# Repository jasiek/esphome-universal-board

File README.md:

# [esphome.io](https://esphome.io)-compatible universal board

* Can control an air conditioning unit and read its remote to display current state of unit.
* Can drive multiple WS2812 LEDs to indicate something.
* Can drive a buzzer to indicate something.
* Notifications using the above can be acknowledged with a click of a button.
* Can read the state of a water meter which uses WMBUS using a CC1101 module.
* Can incorporate additional sensors via I2C.

## Parts

* ESP32 Module [ESP32-S3-WROOM-1](https://www.espressif.com/sites/default/files/documentation/esp32-s3-wroom-1_wroom-1u_datasheet_en.pdf)
* IR Receiver: [TSOP38438](https://www.vishay.com/docs/82491/tsop382.pdf)
* IR Transmitter 850nm @ 165mW: [LL-503SIRC2H-1BE](https://www.tme.eu/Document/bbc76b3f66c79fcebc4b2a3071fa53b8/LL-503SIRC2H-1BE.pdf)
* USB PD Controller: [CH224K](https://www.laskakit.cz/user/related_files/ch224ds1.pdf)
* CC1101 868MHz module: [Small](https://ae01.alicdn.com/kf/H425240e05325482f9e129bee543d8c9eR.jpg) or [Large](https://ae01.alicdn.com/kf/S28ad7d5c77624d52bd05b87e7f74fee7y.jpg)
* Level shifter: [74AHCT1G125](https://www.ti.com/lit/ds/symlink/sn74ahct1g125.pdf)
* Buzzer: [LPT1440S-HS-05](https://www.tme.eu/Document/ccb72bb5ba4b269fcfcf63562faa0900/LPT1440S-HS-05-4.0-12-R.pdf)
* Presence sensors
  * [HLK-LD2450](https://www.tinytronics.nl/product_files/006000_HLK-LD2450-Instruction-Manual.pdf)
  * [HLK-LD2402](https://drive.google.com/file/d/1SmigbSjFt1toA7W5wEuI2Qy-1CSR6PQn/view)
  * [HLK-LD2410](https://www.tinytronics.nl/product_files/006002_HLK-LD2410S_datasheet.pdf)

## Other

* [A Primer on USB Type-C® and USB Power Delivery Applications and Requirements](https://www.ti.com/lit/wp/slyy109b/slyy109b.pdf)

## TODO for rev 3

* Place everything on one side of the board!
* Use SMD electrolytic capacitors.
* Hook up the output of the WS2812 correctly.
* Holes in the board need to be slightly bigger.
* ~~22-33 ohm series resistors on the USB pins: USB-C <-> ESD <-> R <-> USB on ESP32.~~
* ~~Get rid of the 3A PSU circuit.~~
* ~~Replace LED transmitter with a 940nm part, for example TSAL6200 (narrow beam), OSI5LA56A1A, IR7393C (100mA), OSI5NE87B1A, IR323/H0-A, IR8294, OSI5LA7WA1B.~~
* ~~Add another footprint for WS2812B and WS2812S, so that either can be populated~~

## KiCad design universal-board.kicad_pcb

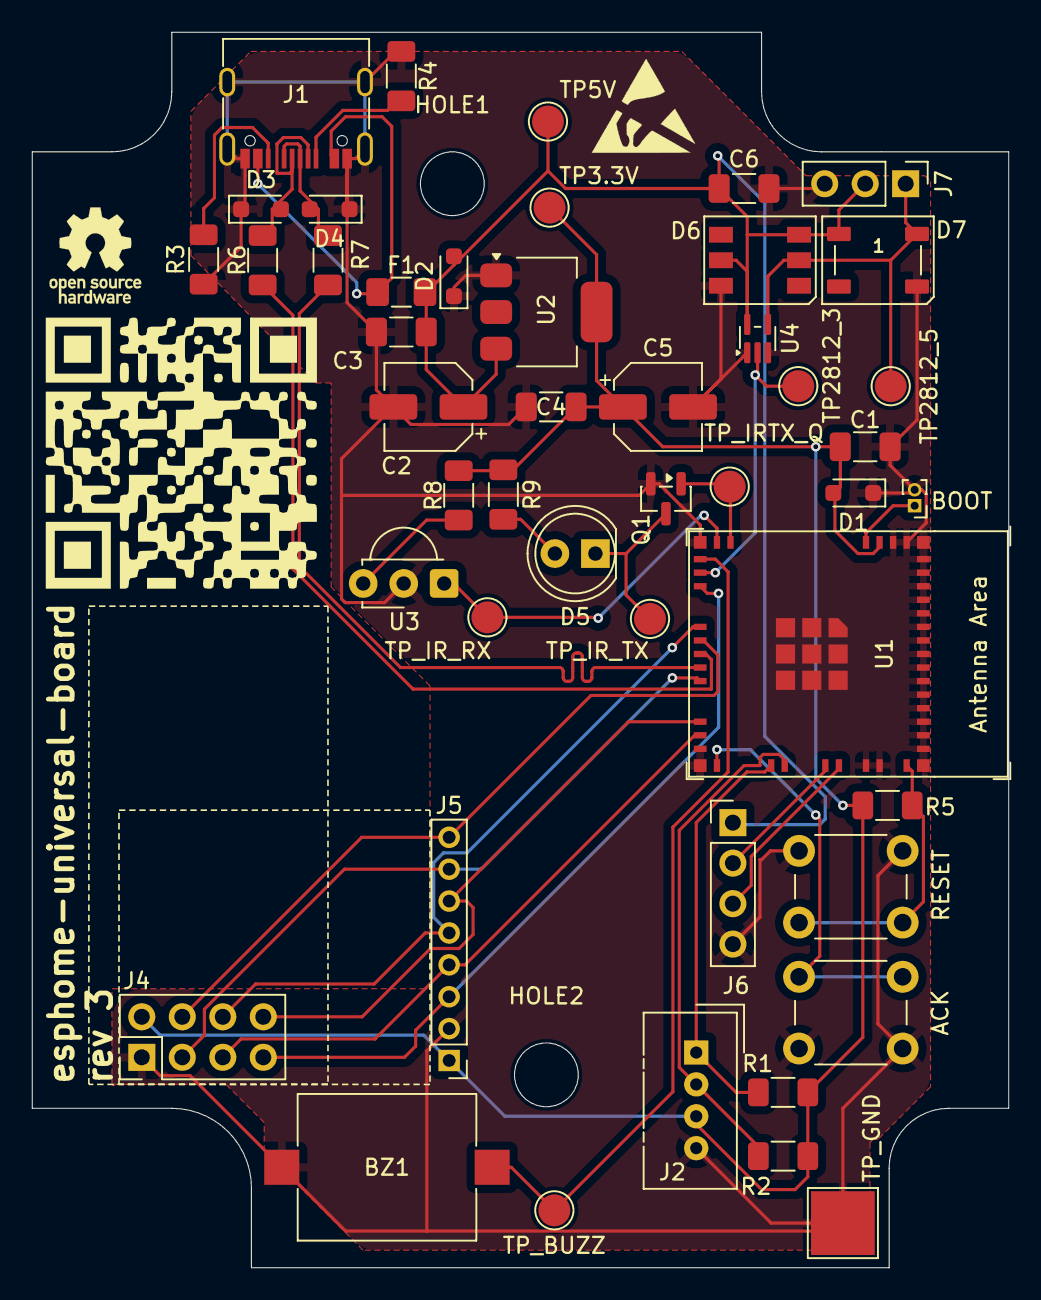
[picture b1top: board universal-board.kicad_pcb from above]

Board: 2 copper layers, 61.2 x 77.5 mm, 49 parts (0 on the bottom side), 31 nets.

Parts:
ACK: SW_ACK; SW_PUSH_6mm
BOOT: CONN_BOOT; PinHeader_1x02_P1.00mm_Vertical
BZ1: LPT1440S-HS-05; Buzzer_Mallory_AST1109MLTRQ
C1, C3, C4, C6: 100nF; C_1206_3216Metric_Pad1.33x1.80mm_HandSolder
C2: 10uF; CP_Elec_5x5.4
C5: 22uF; CP_Elec_5x5.4
D1, D2, D3, D4: PESD5V0L1BA,115-ES; D_SOD-323_HandSoldering
D5: IR7393C; LED_D5.0mm_Clear
D6: WS2812; LED_WS2812_PLCC6_5.0x5.0mm_P1.6mm
D7: WS2812B; LED_WS2812B_PLCC4_5.0x5.0mm_P3.2mm
F1: 0ZCJ0100FF2E (1A); Fuse_1206_3216Metric_Pad1.42x1.75mm_HandSolder
HOLE1, HOLE2: MountingHole_4mm
J1: USB_C_Receptacle; USB_C_Receptacle_G-Switch_GT-USB-7010ASV
J2: CONN_I2C_GROVE; NS-Tech_Grove_1x04_P2mm_Vertical
J4: CONN_CC1101_2; PinHeader_2x04_P2.54mm_Vertical
J5: CONN_CC1101_1; PinHeader_1x08_P2.00mm_Vertical
J6: CONN_UART; PinHeader_1x04_P2.54mm_Vertical
J7: CONN_WS2812; PinHeader_1x03_P2.54mm_Vertical
Q1: BSS138; SOT-23
R1, R2: 4.7k; R_1206_3216Metric_Pad1.30x1.75mm_HandSolder
R3, R4: 5.1k; R_1206_3216Metric_Pad1.30x1.75mm_HandSolder
R5: 10k; R_1206_3216Metric_Pad1.30x1.75mm_HandSolder
R6, R7, R9: 22; R_1206_3216Metric_Pad1.30x1.75mm_HandSolder
R8: 100; R_1206_3216Metric_Pad1.30x1.75mm_HandSolder
RESET: SW_RST; SW_PUSH_6mm
TP3.3V: TP_3.3V; TestPoint_Pad_D2.0mm
TP5V: TP_5V; TestPoint_Pad_D2.0mm
TP2812_3: TP_21812_3.3; TestPoint_Pad_D2.0mm
TP2812_5: TP_2812_5; TestPoint_Pad_D2.0mm
TP_BUZZ: TP_BUZZ; TestPoint_Pad_D2.0mm
TP_GND: TP_GND; TestPoint_Pad_4.0x4.0mm
TP_IRTX_Q: TP_IR_TX; TestPoint_Pad_D2.0mm
TP_IR_RX: TP_IR_RX; TestPoint_Pad_D2.0mm
TP_IR_TX: TP_IR_TX_OUT; TestPoint_Pad_D2.0mm
U1: ESP32-S2-MINI-2; ESP32-S2-MINI-1
U2: AMS1117-3.3; SOT-223-3_TabPin2
U3: TSOP384xx; Vishay_MINICAST-3Pin
U4: 74AHCT1G125; SOT-353_SC-70-5

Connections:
3.3V: C1.1, C4.1, C5.1, D1.2 (A2), J2.3, J4.2, J5.1, R1.2, R2.1, R5.2, R8.1, R9.1, TP3.3V.1, U1.3 (3V3), U2.2 (VO)
5V: C2.1, C3.1, C6.1, D2.2 (A2), D6.3 (VCC), D6.5 (VDD), D7.1 (VDD), F1.2, J6.1, J7.2, TP5V.1, U2.3 (VI), U4.5 (VCC)
BUZZ_OUT: BZ1.1 (+), TP_BUZZ.1, U1.16 (GPIO12/ADC2_CH1)
CSN: J4.4, J5.8, U1.22 (ADC2_CH7/DAC_2/GPIO18)
GDO0: J4.3, J5.7, U1.25 (GPIO21)
GDO2: J4.8, J5.6, U1.28 (GPIO33)
GND: ACK.2 (B), BOOT.2, BZ1.2 (-), C1.2, C2.2, C3.2, C4.2, C5.2, C6.2, D1.1 (A1), D2.1 (A1), D3.1 (A1), D4.1 (A1), D6.6 (VSS), D7.3 (VSS), J1.A1 (GND), J1.A12 (GND), J1.B1 (GND), J1.B12 (GND), J1.S1 (SHIELD), J2.4, J4.1, J5.2, J6.4, J7.3, Q1.2 (S), R3.1, R4.2, RESET.1 (A), TP_GND.1, U1.1 (GND), U1.2 (GND), U1.30 (GND), U1.42 (GND), U1.43 (GND), U1.46 (GND), U1.47 (GND), U1.48 (GND), U1.49 (GND), U1.50 (GND), U1.51 (GND), U1.52 (GND), U1.53 (GND), U1.54 (GND), U1.55 (GND), U1.56 (GND), U1.57 (GND), U1.58 (GND), U1.59 (GND), U1.60 (GND), U1.61 (GND), U1.62 (GND), U1.63 (GND), U1.64 (GND), U1.65 (GND), U2.1 (GND), U3.2 (GND), U4.1, U4.3 (GND)
IR_RX_OUT: TP_IR_RX.1, U1.15 (GPIO11/ADC2_CH0), U3.1 (OUT)
IR_TX_IN: Q1.1 (G), TP_IRTX_Q.1, U1.14 (GPIO10/ADC1_CH9)
MISO: J4.7, J5.3, U1.18 (GPIO14/ADC2_CH3)
MOSI: J4.6, J5.5, U1.21 (ADC2_CH6/DAC_1/GPIO17)
unnamed: D3.2 (A2), J1.A7 (D-), J1.B7 (D-), R6.1
unnamed: D4.2 (A2), J1.A6 (D+), J1.B6 (D+), R7.1
unnamed: D5.2 (A), R9.2
unnamed: D5.1 (K), Q1.3 (D), TP_IR_TX.1
unnamed: D6.2 (DIN), D7.4 (DIN), J7.1, TP2812_5.1, U4.4
unnamed: F1.1, J1.A4 (VBUS), J1.A9 (VBUS), J1.B4 (VBUS), J1.B9 (VBUS)
unnamed: J1.A5 (CC1), R4.1
unnamed: J1.B5 (CC2), R3.2
unnamed: J2.1, R1.1, U1.35 (MTCK/JTAG/GPIO39)
unnamed: J2.2, R2.2, U1.36 (MTDO/JTAG/GPIO40)
unnamed: BOOT.1, U1.4 (GPIO0/BOOT)
unnamed: R5.1, RESET.2 (B), U1.45 (CHIP/PU/RESET)
unnamed: R8.2, U3.3 (Vs)
SCK: J4.5, J5.4, U1.29 (GPIO34)
SW_ACK_OUT: ACK.1 (A), U1.31 (GPIO35)
UART_RX: J6.3, U1.40 (GPIO44/U0RXD/PROG)
UART_TX: J6.2, U1.39 (GPIO43/U0TXD/PROG)
USB+: R7.2, U1.24 (USB_D+/ADC2_CH9/GPIO20)
USB-: R6.2, U1.23 (USB_D-/ADC2_CH8/GPIO19)
WS2818_3.3V_OUT: TP2812_3.1, U1.17 (GPIO13/ADC2_CH2), U4.2

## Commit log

2025-09-10 Added README with parts.
2025-09-10 Schematic for everything.
2025-09-11 Final schematic before review.
2025-09-11 Place ~18–22 Ω (for ~100 mA pulsed) in series with D2.
2025-09-11 Added TVS (SMAJ5.0A) to VBUS-GND Added polyfuses to both PSUs
2025-09-11 Use LPT1440S-HS-05 as the buzzer.
2025-09-11 Shorted DM-DP on the CK224K (pins don't need to be wired up).
2025-09-11 Fixed design error, 5V is connected to VBUS which is the controlled line.
2025-09-11 Added 10k pull-up and 100nF cap between 3.3V/GND for EN.
2025-09-11 Added USBLC6-2SC6 for CC1/CC2 lines.
2025-09-11 Fixed design error IO10 connected to WS2812 input. Added do not connect markers.
2025-09-11 Minor touches.
2025-09-11 Re-labelled all parts.
2025-09-28 ERC fixes.
2025-09-28 Resolved all DRC errors
2025-09-28 - added bidirectional TVS between VBUS & GND - USB-C shield and GND are now connected - added comments re pin order - removed pull-up resistor on SW_ACK_INPUT because it's configured as INPUT_PULLUP
2025-09-28 Tied down CFG2,3 to GND.
2025-09-29 Added decoupling caps for the AMS1117-3.3
2025-09-29 Cap and resistor for TSOP384x
2025-09-29 Added capacitor for ESP32/EN pin
2025-09-29 Moved some components around for better readability.
2025-09-29 Flipped grove connector around
2025-09-29 Updated README.
    Reworked the circuit around CH224K per datasheet an example schematics.
2025-10-02 Makefile for exporting plots.
2025-10-02 Updated .gitignore.
2025-10-02 Fixed export resolution to 300dpi
2025-10-09 Reorganized board to be on one sheet.
2025-10-09 Regenerated schematic.
2025-10-09 Remapped elements
2025-10-09 ERC checks clean.
2025-10-09 Rev 1, added test points
2025-10-10 Partial footprint assignment.
2025-12-17 PCB WIP
2025-12-24 Added UART for HLK modules.
    Updated TODO.
2025-12-25 Removed unused schematics.
2025-12-25 Changed resistor footprints to be actual resistors.
2025-12-25 Added footprint for GCT USB4105-GF-A
2025-12-25 DRC passes on schematic.
2025-12-25 Removed libraries, there are no longer needed.
2025-12-26 PCB is routed, but needs more work.
2025-12-26 Rerouted PCB with freeroute. DRC still pending.
2025-12-26 revision 1 - off to manufacturing
2025-12-26 Updated README and plots.
2025-12-27 - added QR code for test printing - made group labels more prominent - moved some components around to make DRC happy - connected unconnected components (!)
    marked as rev 2
2026-01-29 TODO notes for next revision.
2026-01-30 More notes.
2026-01-30 More notes about IR.
2026-01-30 Added a few more IR options.
2026-01-31 Added critical fix.
2026-01-31 Prep for rev 3:
    - removed 3A PSU
    - added 2 33 ohm resistors for USB
2026-02-03 Added reference designs for ESP32 modules.
    Adjusted IR LED part number.
    Added another WS2812.
2026-02-05 Added TVS diodes to USB and resistors.
2026-02-05 Used ESP32-S2-MINI-2 in place of the curret module.
2026-02-06 Renumbered components.
2026-02-06 Footprints assigned
2026-02-06 Updated part number on schematic for ESP32
2026-02-07 Added another ESD diode.
2026-02-07 First stab at layout for rev 3
2026-02-07 Routing done, pending DRC
2026-02-07 Schematic update (plots).
2026-02-08 Refreshed plot.
2026-02-09 Updated makefile
2026-02-17 Further minor changes to make DRC happy.
2026-03-17 Off to production
2026-04-20 Changed TVS diodes to ElecSuper PESD5V0L1BA,115-ES (bigger, easier to solder).
